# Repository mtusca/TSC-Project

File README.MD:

E-readerul implementat integrează mai multe module esențiale, inclusiv ESP32-C6, un modul RTC, senzori de mediu, 
conectivitate USB-C, un slot pentru card MicroSD și un sistem de gestionare a bateriei. 
Toate componentele comunică prin interfețe standard precum I²C, SPI, UART și GPIO analogice/digitale.

Controler de încărcare – MCP73831
Tip baterie: Li-ion/Li-Po cu o singură celulă

Curent de încărcare: Programabil până la 500 mA

Interfață: Standalone (fără I²C/SPI)

Tensiune de intrare: 3.75 V – 6 V

Ieșire stare: Indicație a stării de încărcare prin LED

Senzor de mediu – BME688
Măsurători: Temperatură, umiditate, presiune, gaze (VOC, calitatea aerului)

Interfață: I²C, SPI

Interval temperatură: -40 °C – +85 °C

Senzor de gaze: Detecție AI a amestecurilor de gaze și VOC

Consum de energie: Ultra redus (ideal pentru dispozitive mobile/wearables)

Display e-paper
Interfață: SPI

Rezoluție: 800×480

Consum de energie: Foarte redus (consum doar în timpul actualizării)

Caracteristici: Lizibil excelent în lumină solară, unghiuri largi de vizualizare

Conector Qwiic
Tip: Conector JST SH cu 4 pini (1.0 mm)

Scop: Interconectare I²C standardizată pentru senzori/module

Tensiune: Logică de 3.3 V

Pini: SDA, SCL, VCC, GND

Conector card memorie – 112A-TAAR-R03
Tip: Slot pentru card MicroSD

Interfață: SPI sau SDIO

Tensiune: Logică 3.3 V

Caracteristici: Mecanism push-push, contact pentru detectare card

Utilizare: Stocare de date, redare media

Microcontroler – ESP32-C6-WROOM-1-N8
Procesor: RISC-V pe 32 de biți, până la 160 MHz

Memorie: 512 KB SRAM intern, 8 MB flash extern (W25Q512JVEIQ)

Conectivitate: Wi-Fi 6 (802.11ax), Bluetooth 5 (LE), IEEE 802.15.4 (Thread/Zigbee), USB 2.0 (Full-Speed)

Periferice: SPI, I²C, UART, PWM, ADC, mai mulți pini GPIO

Memorie externă – W25Q512JVEIQ
Capacitate: 512 Mbit (64 MB)

Interfață: Quad SPI (QPI)

Frecvență de operare: Până la 133 MHz

Tensiune de alimentare: 2.7 V – 3.6 V

Caracteristici: rezistență mare (100.000 cicluri scriere/ștergere)

Ceas în timp real – DS3231SN#
Precizie: ±2 ppm între 0°C și +40°C

Interfață: I²C

Caracteristici: Oscilator cu cristal compensat termic (TCXO) integrat

Tensiune de funcționare: 2.3 V – 5.5 V

Funcționalități suplimentare: suport pentru baterie de rezervă, 2 alarme programabile, ieșire pătrată 1Hz

Monitor baterie – MAX17048G+T10
Funcție: Indicator de încărcare pentru baterii Li-ion/Li-Po cu o singură celulă

Interfață: I²C

Tensiune: 2.5 V – 4.5 V

Consum de putere: Curent de repaus ultra-redus (~23 µA)

<pre lang="markdown"> 
ESP32-C6 Pin description
  EN -> Resets the MCU
  IO0 - INT_RTC -> Used to receive interrupts signals from RTC, allowing for two major functionalities: Alarm and Square Wave Output
  IO1 - 32KHz -> Used for a stable clock signal of 32.768 kHz generated by the RTC
  IO2 – MISO -> Master In Slave Out Signal, used in the SPI communication with the SD Card
  IO3 - EPD_BUSY -> Indicates display driver status
  IO4 – SS_SD -> Chip select for SPI communication with SD Card
  IO5 – EPD_DC -> Display serial communication Command/Data input
  IO6 – SCK -> Clock signal for I2C communication
  IO7 – MOSI -> Master Out Slave In Signal, used to send data to display and SD Card
  IO8 - GPIO8 - Controls MCU boot mode
  IO9 - IO/BOOT -> Used to detect BOOT button press
  NC -> Not connected
  3V3 -> Used to power the MCU and the other components
  IO10 - EPD_CS -> Chip select for SPI serial communication with the display
  IO11 - FLASH_CS -> Chip select for SPI communication with the flash
  IO12 - USB_D- -> Used in USB differential communication
  IO13 - USB_D+ -> Used in USB differential communication
  IO15 - IO/CHANGE -> Used to detect CHANGE button press
  TXD0/GPIO16 - TX -> Sends data to another device via UART
  RXD0/GPIO17 - RX -> Receives data from another device via UART
  IO18 - RTC_RST -> Resets the RTC
  IO19 - I2C_PW -> Power source for I2C components
  IO20 - EPD_3V3_C -> Display IO voltage supply
  IO21 - SDA -> Used to send and receive data in the I2C communication with the sensor, RTC module and Battery Fuel Gauge
  IO22 - SCL -> Clock signal for I2C communication
  IO23 - EPD_RST -> Global reset signal for the display
  GND -> Shared Voltage Reference
</pre>

[📋 Download BoM](./Manufacturing/Bill%20of%20Materials.csv)

|Component    |Footprint                                    |Link                                                                                                        |
|-------------|---------------------------------------------|------------------------------------------------------------------------------------------------------------|
|BOOT_BUTTON  |BUTTON_CUSYOMV1                              |https://industry.panasonic.com/global/en/products/control/switch/light-touch/number/evqpuj02k               |
|C1           |ESP32_WROVER_EAGLE-LTSPICE_CC0402            |https://eu.mouser.com/ProductDetail/YAGEO/CC0402MRX5R5BB106?qs=zEY9bCHj09eCmUJdZuS5Lg%3D%3D                 |
|C1_BAT       |ESP32_WROVER_EAGLE-LTSPICE_CC0402            |n/a                                                                                                         |
|C1_BAT1      |EAGLE-LTSPICE_CC0402                         |n/a                                                                                                         |
|C1_BAT2      |EAGLE-LTSPICE_CC0402                         |n/a                                                                                                         |
|C2           |ESP32_WROVER_EAGLE-LTSPICE_CC0402            |n/a                                                                                                         |
|C2_BAT\      |ESP32_WROVER_EAGLE-LTSPICE_CC0402            |n/a                                                                                                         |
|C3           |RCL_CPOL-EUCT3528                            |n/a                                                                                                         |
|C4           |ESP32_WROVER_EAGLE-LTSPICE_CC0402            |n/a                                                                                                         |
|C4_USB       |ESP32_WROVER_EAGLE-LTSPICE_CC0402            |n/a                                                                                                         |
|C5           |ESP32_WROVER_EAGLE-LTSPICE_CC0402            |n/a                                                                                                         |
|C5_USB       |ESP32_WROVER_EAGLE-LTSPICE_CC0402            |n/a                                                                                                         |
|C6           |ESP32_WROVER_EAGLE-LTSPICE_CC0402            |n/a                                                                                                         |
|C7           |ESP32_WROVER_EAGLE-LTSPICE_CC0402            |n/a                                                                                                         |
|C8           |ESP32_WROVER_EAGLE-LTSPICE_CC0402            |n/a                                                                                                         |
|C9           |EAGLE-LTSPICE_CC0402                         |n/a                                                                                                         |
|C10          |ESP32_WROVER_EAGLE-LTSPICE_CC0402            |n/a                                                                                                         |
|C10_SUPERCAP |CPH3225A                                     |https://www.snapeda.com/parts/CPH3225A/Seiko+Instruments/view-part/?ref=eda                                 |
|CHANGE_BUTTON|BUTTON_CUSYOMV1                              |https://industry.panasonic.com/global/en/products/control/switch-light-touch/number/evqpuj02k               |
|CHG_LED      |ADAFRUIT_LEDCHIP-LED0603                     |https://www.snapeda.com/parts/KP-1608SURCK/Kingbright/view-part/?ref=search&t=LED%200603                    |
|C_DELAY      |ESP32_WROVER_EAGLE-LTSPICE_CC0402            |n/a                                                                                                         |
|D1           |USBLC6-2SC6Y                                 |https://www.snapeda.com/parts/USBLC6-2SC6Y/STMicroelectronics/view-part/?ref=eda                            |
|D2           |ESP32_WROVER_AVX---SD0805S020S1R0_AVX_...    |https://eu.mouser.com/ProductDetail/KYOCERA-AVX/SD0805S020S1R0?qs=jCA%252BPfw4LHbpkAoSnwrdjw%3D%3D          |
|D3           |MBR0530                                      |https://eu.mouser.com/ProductDetail/KYOCERA-AVX/SD0805S020S1R0?qs=jCA%252BPfw4LHbpkAoSnwrdjw%3D%3D          |
|D4           |MBR0530                                      |https://www.snapeda.com/parts/MBR0530/Onsemi/view-part/?ref=eda                                             |
|D5           |MBR0530                                      |https://www.snapeda.com/parts/MBR0530/Onsemi/view-part/?ref=eda                                             |
|D6           |PGB1010603MR                                 |https://www.snapeda.com/parts/PGB1010603MR/Littelfuse/view-part/?ref=eda                                    |
|D7           |ESP32_WROVER_AVX---SD0805S020S1R0_AVX_...    |https://eu.mouser.com/ProductDetail/KYOCERA-AVX/SD0805S020S1R0?qs=jCA%252BPfw4LHbpkAoSnwrdjw%3D%3D          |
|D8           |PGB1010603MR                                 |https://www.snapeda.com/parts/PGB1010603MR/Littelfuse/view-part/?ref=eda                                    |
|D9           |PGB1010603MR                                 |https://www.snapeda.com/parts/PGB1010603MR/Littelfuse/view-part/?ref=eda                                    |
|D10          |PGB1010603MR                                 |https://www.snapeda.com/parts/PGB1010603MR/Littelfuse/view-part/?ref=eda                                    |
|D11          |PGB1010603MR                                 |https://www.snapeda.com/parts/PGB1010603MR/Littelfuse/view-part/?ref=eda                                    |
|D12          |PGB1010603MR                                 |https://www.snapeda.com/parts/PGB1010603MR/Littelfuse/view-part/?ref=eda                                    |
|EPD_C1       |ESP32_WROVER_EAGLE-LTSPICE_CC0402            |n/a                                                                                                         |
|EPD_C2       |ESP32_WROVER_EAGLE-LTSPICE_CC0402            |n/a                                                                                                         |
|EPD_C5       |ESP32_WROVER_EAGLE-LTSPICE_CC0402            |n/a                                                                                                         |
|EPD_C6       |ESP32_WROVER_EAGLE-LTSPICE_CC0402            |n/a                                                                                                         |
|EPD_C7       |ESP32_WROVER_EAGLE-LTSPICE_CC0402            |n/a                                                                                                         |
|EPD_C8       |ESP32_WROVER_EAGLE-LTSPICE_CC0402            |n/a                                                                                                         |
|EPD_C9       |ESP32_WROVER_EAGLE-LTSPICE_CC0402            |n/a                                                                                                         |
|EPD_C10      |ESP32_WROVER_EAGLE-LTSPICE_CC0402            |n/a                                                                                                         |
|EPD_C11      |ESP32_WROVER_EAGLE-LTSPICE_CC0402            |n/a                                                                                                         |
|EPD_C12      |ESP32_WROVER_EAGLE-LTSPICE_CC0402            |n/a                                                                                                         |
|IC1          |BD5229G-TR                                   |https://componentsearchengine.com/part-view/BD5229G-TR/ROHM%20Semiconductor                                 |
|IC4          |XC6220A331MR-G                               |https://componentsearchengine.com/part-view/XC6220A331MR-G/Torex                                            |
|J1           |FH34SRJ-24S-0.5SH_99_                        |https://componentsearchengine.com/part-view/XC6220A331MR-G/Torex                                            |
|J2           |SAMACSYS_PARTS_USB4110-GF-A                  |https://componentsearchengine.com/part-view/USB4110-GF-A/GCT%20(GLOBAL%20CONNECTOR%20TECHNOLOGY             |
|J3           |QWIIC_CONNECTORJS-1MM                        |n/a                                                                                                         |
|J4           |112A-TAAR-R03_ATTEND                         |https://store.comet.srl.ro/Catalogue/Product/43497/                                                         |
|L1           |744043680IND_4828-WE-TPC_WRE                 |https://eu.mouser.com/ProductDetail/Wurth-Elektronik/744043680?qs=PGXP4M47uW6VkZq%252BkzjrHA%3D%3D          |
|PFMF.050.1   |ESP32C6_VARISTORCN1812                       |https://www.mouser.co.uk/ProductDetail/EPCOS-TDK/B72520T0350K062?qs=dEfas%2FXlABIszF52uu7vrg%3D%3D          |
|Q1           |ESP32_WROVER_SPARKFUN-DISCRETESEMI_MOSFET_...|https://componentsearchengine.com/part-view/DMG2305UX-7/Diodes%20Incorporated                               |
|Q2           |ESP32_WROVER_SPARKFUN-DISCRETESEMI_MOSFET_...|n/a                                                                                                         |
|Q3           |D8                                           |https://componentsearchengine.com/part-view/SI1308EDL-T1-GE3/Vishay                                         |
|R1           |ESP32_WROVER_EAGLE-LTSPICE_RR0402            |n/a                                                                                                         |
|R1-PINH      |ESP32_WROVER_EAGLE-LTSPICE_RR0402            |n/a                                                                                                         |
|R1-PINH1     |ESP32_WROVER_EAGLE-LTSPICE_RR0402            |n/a                                                                                                         |
|R1_BAT       |ESP32_WROVER_EAGLE-LTSPICE_RR0402            |n/a                                                                                                         |
|R1_PWRUSB    |ESP32_WROVER_EAGLE-LTSPICE_RR0402            |n/a                                                                                                         |
|R2           |ESP32_WROVER_EAGLE-LTSPICE_RR0402            |https://componentsearchengine.com/part-view/R0402%201%25%20100%20K%20(RC0402FR-07100KL                      |
|R2-PINH      |ESP32_WROVER_EAGLE-LTSPICE_RR0402            |n/a                                                                                                         |
|R2-PINH1     |ESP32_WROVER_EAGLE-LTSPICE_RR0402            |n/a                                                                                                         |
|R2-USB       |ESP32_WROVER_EAGLE-LTSPICE_RR0402            |n/a                                                                                                         |
|R2-USB1      |ESP32_WROVER_EAGLE-LTSPICE_RR0402            |n/a                                                                                                         |
|R2_BAT       |ESP32_WROVER_EAGLE-LTSPICE_RR0402            |n/a                                                                                                         |
|R3           |ESP32_WROVER_EAGLE-LTSPICE_RR0402            |n/a                                                                                                         |
|R4           |ESP32_WROVER_EAGLE-LTSPICE_RR0402            |n/a                                                                                                         |
|R5           |ESP32_WROVER_EAGLE-LTSPICE_RR0402            |n/a                                                                                                         |
|R6           |ESP32_WROVER_EAGLE-LTSPICE_RR0402            |n/a                                                                                                         |
|R7           |ESP32_WROVER_EAGLE-LTSPICE_RR0402            |n/a                                                                                                         |
|R8           |ESP32_WROVER_EAGLE-LTSPICE_RR0402            |n/a                                                                                                         |
|R9           |ESP32_WROVER_EAGLE-LTSPICE_RR0402            |n/a                                                                                                         |
|R10          |ESP32_WROVER_EAGLE-LTSPICE_RR0402            |n/a                                                                                                         |
|RESET_BUTTON |BUTTON_CUSYOMV1                              |https://industry.panasonic.com/global/en/products/control/switch/light-touch/number/evqpuj02k               |
|R_BOOT       |ESP32_WROVER_EAGLE-LTSPICE_RR0402            |n/a                                                                                                         |
|R_CAPACITOR  |ESP32_WROVER_EAGLE-LTSPICE_RR0402            |n/a                                                                                                         |
|R_CHANGE     |ESP32_WROVER_EAGLE-LTSPICE_RR0402            |n/a                                                                                                         |
|R_CL1        |ESP32_WROVER_EAGLE-LTSPICE_RR0402            |n/a                                                                                                         |
|R_RESET      |ESP32_WROVER_EAGLE-LTSPICE_RR0402            |n/a                                                                                                         |
|SENSOR2      |ESP32_WROVER_BME680_BME680                   |https://www.snapeda.com/parts/BME680/Bosch/view-part/?welcome=home                                          |
|SJ1          |SJ                                           |https://grabcad.com/library/solder-jumpers-1                                                                |
|U1           |W25Q512JVEIQ                                 |https://www.snapeda.com/parts/W25Q512JVEIQ/Winbond+Electronics/view-part/?ref=eda                           |
|U2           |ESP32-C6-WROOM-1-N8                          |https://www.snapeda.com/parts/ESP32-C6-WROOM-1-N8/Espressif+Systems/view-part/?ref=eda                      |
|U3           |DS3231SN#                                    |https://www.snapeda.com/parts/DS3231SN%23/Analog+Devices/view-part/?ref=eda                                 |
|U4           |MAX17048G+T10                                |https://www.snapeda.com/parts/MAX17048G+T10/Analog+Devices/view-part/?ref=eda                               |
|U5           |ESP32_WROVER_SPARKFUN-IC-POWER_MCP73831      |https://eu.mouser.com/ProductDetail/Microchip-Technology/MCP73831T-2ACI-OT?qs=yUQqVecv4qvbBQBGbHx0Mw%3D%3Dcf|

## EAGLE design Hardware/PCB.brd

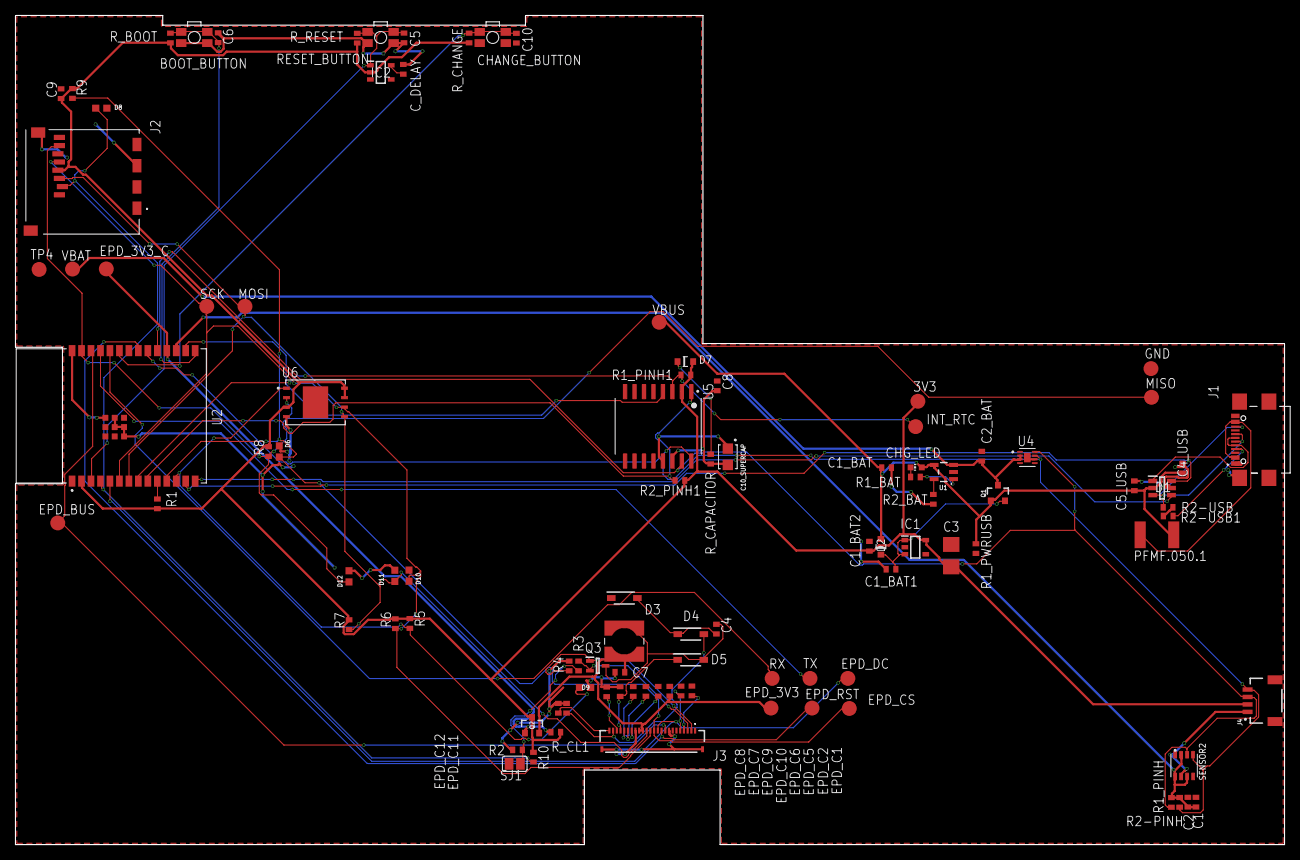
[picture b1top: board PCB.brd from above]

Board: 2 copper layers, 170.2 x 111.2 mm, 103 parts (0 on the bottom side), 55 nets.

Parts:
3V3: TP; TP20R
BOOT_BUTTON: BUTTON_CUSYOMV1NEW; MYBUTTON
C1, C2, C4_USB, C6, C8, C9, C10: 100nF; ESP32_WROVER_EAGLE-LTSPICE_C0402
C1_BAT, C1_BAT1, C1_BAT2, C2_BAT, C5_USB: 4.7uF; ESP32_WROVER_EAGLE-LTSPICE_C0402
C3: 100uF TANT; RCL_CT3528
C4: 4.7uF/25V; ESP32_WROVER_EAGLE-LTSPICE_C0402
C5: 1uF; ESP32_WROVER_EAGLE-LTSPICE_C0402
C7: 10uF; ESP32_WROVER_EAGLE-LTSPICE_C0402
C10_SUPERCAP: CPH3225A; CAPCP3225X100N
CHANGE_BUTTON: BUTTON_CUSYOMV1NEW; MYBUTTON
CHG_LED: ADAFRUIT_CHIP-LED0603
C_DELAY: 100nF; ESP32_WROVER_EAGLE-LTSPICE_C0402
D1: USBLC6-2SC6Y; SOT95P280X145-6N
D2, D7: ESP32_WROVER_AVX---SD0805S020S1R0_AVX_SD0805S020S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; ESP32_WROVER_AVX---SD0805S020S1R0_AVX_SD0805S020S1R0_0
D3, D4, D5: MBR0530; SOD3716X135N
D6, D8, D9, D10, D11, D12: PGB1010603MRNEW; DIOC1608X36N
EPD_3V3, EPD_3V3_C: TP; TP20R
EPD_BUS: TP; TP20R
EPD_C1, EPD_C2, EPD_C6, EPD_C7, EPD_C8, EPD_C9, EPD_C10, EPD_C11, EPD_C12: 1uF/50V; ESP32_WROVER_EAGLE-LTSPICE_C0402
EPD_C5: 0.1uF/50V; ESP32_WROVER_EAGLE-LTSPICE_C0402
EPD_CS: TP; TP20R
EPD_DC: TP; TP20R
EPD_RST: TP; TP20R
GND: TP; TP20R
IC1: XC6220A331MR-G; SOT95P280X120-5N
IC2: BD5229G-TR; SOT95P280X125-5N
INT_RTC: TP; TP20R
J1: SAMACSYS_PARTS_USB4110-GF-A; SAMACSYS_PARTS_USB4110GFA
J2: 112A-TAAR-R03_ATTEND; 112ATAARR03ATTEND
J3: FH34SRJ-24S-0.5SH_99_; FH34SRJ24S05SH99
J4: QWIIC_RIGHT_ANGLE; JST04_1MM_RA
L1: 68uH; IND_4828-WE-TPC_WRE
MISO: TP; TP20R
MOSI: TP; TP20R
PFMF.050.1: ESP32C6_VARISTORCN1812; ESP32C6_VARISTOR_CT/CN1812
Q1, Q2: 20V/4.2A/52mΩ/1.4W; ESP32_WROVER_SPARKFUN-DISCRETESEMI_SOT23-3
Q3: SI1308EDL-T1-GE3; SOT65P210X110-3N
R1, R1_PINH, R1_PINH1, R2-PINH, R2_PINH1, R4, R5, R6, R7, R8, R9, R10: 10K; ESP32_WROVER_EAGLE-LTSPICE_R0402
R1_BAT: 200; ESP32_WROVER_EAGLE-LTSPICE_R0402
R1_PWRUSB: 100k; ESP32_WROVER_EAGLE-LTSPICE_R0402
R2: 2.2; ESP32_WROVER_EAGLE-LTSPICE_R0402
R2-USB: 5k1; ESP32_WROVER_EAGLE-LTSPICE_R0402
R2-USB1: 5K1; ESP32_WROVER_EAGLE-LTSPICE_R0402
R2_BAT: 2K; ESP32_WROVER_EAGLE-LTSPICE_R0402
R3: 0.47; ESP32_WROVER_EAGLE-LTSPICE_R0402
RESET_BUTTON: BUTTON_CUSYOMV1NEW; MYBUTTON
RX: TP; TP20R
R_BOOT: 10K; ESP32_WROVER_EAGLE-LTSPICE_R0402
R_CAPACITOR: 15; ESP32_WROVER_EAGLE-LTSPICE_R0402
R_CHANGE: 10K; ESP32_WROVER_EAGLE-LTSPICE_R0402
R_CL1: 10K; ESP32_WROVER_EAGLE-LTSPICE_R0402
R_RESET: 10K; ESP32_WROVER_EAGLE-LTSPICE_R0402
SCK: TP; TP20R
SENSOR2: ESP32_WROVER_BME680_BME680; ESP32_WROVER_BME680_PSON80P300X300X100-8N
SJ1: SJ
TP4: TP; TP20R
TX: TP; TP20R
U1: ESP32_WROVER_SPARKFUN-IC-POWER_MCP73831; ESP32_WROVER_SPARKFUN-IC-POWER_SOT23-5
U2: ESP32-C6-WROOM-1-N8; XCVR_ESP32-C6-WROOM-1-N8
U4: MAX17048G+T10; SON50P200X200X80-9N
U5: DS3231SN#; SOIC127P1032X265-16N
U6: W25Q512JVEIQ; SON127P600X800X80-9N
VBAT: TP; TP20R
VBUS: TP; TP20R

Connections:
3V3: 3V3.TP, C1_BAT2.1, C3.+, C9.1, D7.2, IC1.5, IC2.2, J2.P4, J4.2, Q2.3, R1.2, R1_PINH1.2, R2_PINH1.2, R5.2, R6.2, R7.2, R8.2, R9.2, R10.2, R_BOOT.2, R_CHANGE.2, R_CL1.2, R_RESET.2, U2.2, U5.2, U6.3, U6.7, U6.8
32KHZ: R2_PINH1.1, U2.9, U5.1
DN: D1.1, J1.A7, J1.B7
DP: D1.3, J1.A6, J1.B6
EPD_3V3: C7.1, EPD_3V3.TP, EPD_C5.2, J3.15, J3.16, L1.2, Q2.2
EPD_3V3_C: EPD_3V3_C.TP, Q2.1, R_CL1.1, U2.18
EPD_BUSY: EPD_BUS.TP, J3.9, U2.26
EPD_CS: D6.1, EPD_CS.TP, J3.12, R9.1, U2.11
EPD_DC: EPD_DC.TP, J3.11, U2.5
EPD_RST: EPD_RST.TP, J3.10, U2.21
FLASH_CS: D9.1, R5.1, U2.12, U6.1
GDR: J3.2, Q3.1, R4.2
GND: BOOT_BUTTON.1, BOOT_BUTTON.2, C1.2, C1_BAT.2, C1_BAT1.2, C1_BAT2.2, C2.2, C2_BAT.2, C3.-, C4_USB.2, C5.2, C5_USB.2, C6.2, C7.2, C8.2, C9.2, C10.2, C10_SUPERCAP.1, CHANGE_BUTTON.1, CHANGE_BUTTON.2, C_DELAY.2, D1.5, D3.1, D6.2, D8.2, D9.2, D10.2, D11.2, D12.2, EPD_C1.1, EPD_C2.1, EPD_C5.1, EPD_C6.1, EPD_C7.1, EPD_C8.1, EPD_C9.1, EPD_C10.1, EPD_C11.1, EPD_C12.1, GND.TP, IC1.2, IC2.3, J1.A1, J1.A12, J1.B1, J1.B12, J1.MP1, J1.MP2, J1.MP3, J1.MP4, J2.G1, J2.G2, J2.G3, J2.G4, J2.P6, J3.8, J3.17, J3.MP1, J3.MP2, J4.1, R1_PWRUSB.1, R2.1, R2-USB.2, R2-USB1.1, R2_BAT.1, R4.1, RESET_BUTTON.1, RESET_BUTTON.2, SENSOR2.1, SENSOR2.5, SENSOR2.7, SJ1.1, TP4.TP, U1.2, U2.1, U2.28, U2.29_1, U2.29_2, U2.29_3, U2.29_4, U2.29_5, U2.29_6, U2.29_7, U2.29_8, U2.29_9, U4.1, U4.4, U4.6, U4.9, U5.13, U6.4, U6.9
GPIO8: R1.1, U2.10
I2C_PW: C1.1, C2.1, R1_PINH.2, R2-PINH.2, SENSOR2.2, SENSOR2.6, SENSOR2.8, U2.17
INT_RTC: INT_RTC.TP, R1_PINH1.1, U2.8, U5.3
IO/BOOT: BOOT_BUTTON.3, BOOT_BUTTON.4, C6.1, R_BOOT.1, U2.15
IO/CHANGE: C10.1, CHANGE_BUTTON.3, CHANGE_BUTTON.4, R_CHANGE.1, U2.23
MISO: D12.1, J2.P7, MISO.TP, R8.1, U2.27, U6.2
MOSI: D11.1, J2.P3, J3.14, MOSI.TP, R7.1, U2.7, U6.5
unnamed: EPD_C12.2, J3.24
unnamed: C1_BAT1.1, D2.1, IC1.1, IC1.3, Q1.2
unnamed: J1.A5, R2-USB1.2
unnamed: CHG_LED.C, R1_BAT.1
unnamed: C4.1, D3.2, D4.1
unnamed: R1_BAT.2, U1.1
unnamed: R2_BAT.2, U1.5
unnamed: EPD_C10.2, J3.22
unnamed: C_DELAY.1, IC2.5
unnamed: J1.B5, R2-USB.1
unnamed: EPD_C8.2, J3.20
unnamed: EPD_C7.2, J3.19
unnamed: EPD_C6.2, J3.18
unnamed: D7.1, R_CAPACITOR.1
unnamed: EPD_C2.2, J3.5
unnamed: EPD_C1.2, J3.4
PREVGH: D5.1, EPD_C9.2, J3.21
PREVGL: D4.2, EPD_C11.2, J3.23
RESE: J3.3, Q3.2, R3.2
RESE': R2.2, R3.1, SJ1.2
RESET: C5.1, IC2.1, RESET_BUTTON.3, RESET_BUTTON.4, R_RESET.1, U2.3
RTC_RST: U2.16, U5.4
RX: RX.TP, U2.24
SCK: D10.1, J2.P5, J3.13, R6.1, SCK.TP, U2.6, U6.6
SCL: J4.4, R2-PINH.1, SENSOR2.4, U2.20, U4.7, U5.16
SDA: J4.3, R1_PINH.1, SENSOR2.3, U2.19, U4.8, U5.15
SRC: C4.2, D5.2, L1.1, Q3.3
SS_SD: D8.1, J2.P2, R10.1, U2.4
TX: TX.TP, U2.25
USB_D+: D1.4, U2.14
USB_D-: D1.6, U2.13
VBAT: C2_BAT.1, Q1.3, U1.3, U4.2, U4.3, VBAT.TP
VBUS: C1_BAT.1, C4_USB.1, C5_USB.1, CHG_LED.A, D1.2, D2.2, PFMF.050.1.2, Q1.1, R1_PWRUSB.2, U1.4, VBUS.TP
VRTC: C8.1, C10_SUPERCAP.2, R_CAPACITOR.2, U5.14
VUSB: J1.A4, J1.A9, J1.B4, J1.B9, PFMF.050.1.1

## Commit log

2025-04-06 Create LICENSE

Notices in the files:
parts and their libraries:
COPYRIGHT: Copyright (C) 2024 Ultra Librarian. All rights reserved.
